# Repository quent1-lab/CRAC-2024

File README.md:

# Le LIDAR

Ce projet à été créer afin de répondre au besoin lié à la coupe de robotique de France 2024. Avec pour thème : Farming Mars

## Structure du projet

Le projet est organisé en plusieurs dossiers :

- `Lidar` : Contient le code python principal pour le fonctionnement du LIDAR. 
- `Lidarobot` : Contient le code C++ de la base roulante
- `PCB_CAN` : Contient le projet de la carte PCB CAN
- `Rapport S3` : Contient le rapport de projet
- `WIFI` : Contient des scripts simple pour tester la communication par socket et le principe du multitâche
- `CAN` : Contient un scripts simple pour tester la communication CAN
- `3D démonstrateur` : Contient les fichers STL et les GCODE correspondant à l'imprimante Ender-3 v2

## Installation

Vous pouvez cloner le projet via git en utilisant la commande suivante :

```bash
  git clone https://github.com/quent1-lab/CRAC-2024
```

Ensuite, naviguez dans le dossier du projet et installez les dépendances nécessaires avec pip :
```bash
  pip install -r requirements.txt
```
    
## Déploiement

Le fonctionnement de cette version du code nécessite un ordinateur connecté en série avec la base roulante, et le lidar connecté à la Raspberry Pi. 
Les deux appareils doivent être connecté au même réseau WIFI (Attention à bien modifier l'adresse IP du serveur sur le fichier `lidar_Rasp.py`).

Dans l'ordre, il faut lancer :
 - le programme python `LidarScan.py` sur l'ordinateur (car c'est le serveur)
```bash
  python Lidar/LidarScan.py
```
 - Le programme python `lidar_Rasp.py` sur la Raspberry Pi
```bash
  python Lidar/lidar_Rasp.py
```

## Authors

- [@quent1-lab](https://github.com/quent1-lab)

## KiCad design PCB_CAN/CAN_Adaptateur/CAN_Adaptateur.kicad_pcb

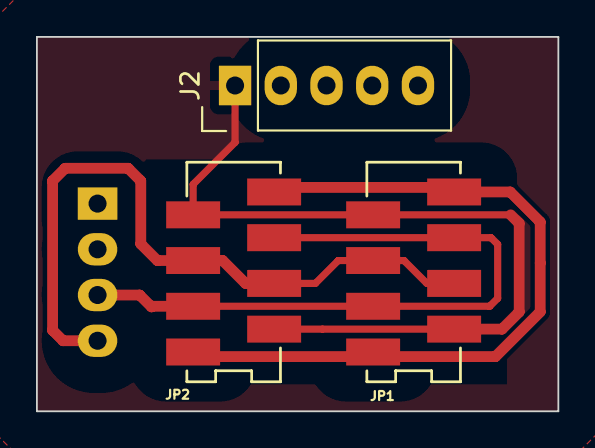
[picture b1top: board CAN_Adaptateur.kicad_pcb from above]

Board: 2 copper layers, 29.0 x 20.8 mm, 4 parts (1 on the bottom side), 3 nets.

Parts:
J1: Autocom4
J2: Autocom5
JP1: Can_1; MM 8 CMS F
JP2: Can_2; MM 8 CMS F

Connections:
/CAN_H: J1.4, JP1.4 (CAN_H), JP1.5 (CAN_H), JP2.4 (CAN_H), JP2.5 (CAN_H)
/CAN_L: J1.3, JP1.3 (CAN_L), JP1.6 (CAN_L), JP2.3 (CAN_L), JP2.6 (CAN_L)
GND: J2.1, JP1.2 (GND), JP1.7 (GND), JP2.2 (GND), JP2.7 (GND)

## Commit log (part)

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2024-05-05 chore: Activer l'asservissement lorsque le switch 3 est activé
2024-05-05 chore: Update CAN message ID for activating the asservissement
2024-05-05 chore: Update path to strategies folder in IHM_Robot.py
2024-05-05 chore: Update coordinates mapping in IHM and Lidar classes
2024-05-05 chore: Update LidarScanner class to remove unnecessary logging statement
2024-05-05 chore: Update LidarScanner class to adjust angle calculation
    ```
2024-05-05 chore: Update LidarScanner class angle calculation and coordinates mapping
2024-05-05 chore: Update coordinates mapping in LidarScanner class
2024-05-05 chore: Adjust angle calculation and remove unnecessary logging statement in LidarScanner class
2024-05-05 chore: Adjust angle calculation in LidarScanner class
2024-05-05 chore: Adjust angle calculation and update position update method in LidarScanner class
2024-05-05 chore: Refactor LidarScanner class position update method and angle calculation
2024-05-05 chore: Update Strategie class with timer functionality for stopping the strategy after a certain time
2024-05-05 chore: Update IHM_Robot class to use strategies from the strategies_cache directory
2024-05-05 chore: Update button position in IHM_Robot class
2024-05-05 chore: Update IHM_Robot class to include match page and points page
2024-05-06 chore: Update IHM_Robot class to include new buttons for recalibration
2024-05-06 chore: Update IHM_Robot class to reset PAGE value when zone is 0
2024-05-06 chore: Update IHM_Robot class to include lazy loading for images
2024-05-06 chore: Update button_recalage action in IHM_Robot class
2024-05-06 chore: Update button_recalage action and positions in IHM_Robot class
2024-05-06 chore: Update IHM_Robot class to include folder creation for recalages_cache
2024-05-06 chore: Update robot image scaling and position handling in IHM_Robot class
2024-05-06 chore: Update JSON files with new aknowledge values and modify CAN.py for set_odo command
2024-05-06 chore: Add logging statements for debugging CAN message handling
2024-05-06 chore: Update IHM_Robot.py for recalibration feature
2024-05-06 chore: Update CAN.py to send messageCan in ComCAN class
2024-05-06 chore: Update recalage_2.json for CAN recalibration feature
2024-05-06 chore: Update strategie.json and Lidar.py
2024-05-06 chore: Update Lidar.py to adjust angle range for scanning
2024-05-06 chore: Reset actionneur carte and start jack
2024-05-07 chore: Update IHM_Robot.py to display code version in the bottom right corner
2024-05-07 chore: Update IHM_Robot.py to adjust code version display position
2024-05-07 chore: Update IHM_Robot.py to remove unused imports and clean up code formatting
2024-05-07 chore: Update strategie.json and Lidar.py to handle empty data
2024-05-07 chore: Filter out low-quality lidar points in LidarScanner class
2024-05-07 chore: Update IHM_Robot.py to version 1.025
2024-05-07 chore: Update Lidar.py to filter out lidar points with quality below 530
2024-05-07 chore: Update Lidar.py to filter out lidar points with quality below 25
2024-05-07 chore: Update IHM_Robot.py to send the correct configuration message
2024-05-07 chore: Update Strategie.py to log received configuration and sent position
2024-05-07 chore: Bump IHM_Robot version to 1.027
2024-05-07 chore: Update Strategie.py to fix position calculation for yellow team
2024-05-07 chore: Update IHM_Robot.py and Lidar.py to improve LiDAR scanning process
2024-05-08 chore: Update Lidar.py detect_objects parameters for better object detection
2024-05-08 chore: Update Lidar.py to filter out points with significantly different distances from neighboring points
2024-05-08 chore: Update IHM_Robot.py version to 1.033 and run strategie 3 in Strategie.py
2024-05-08 Fix commented out code in Strategie.py
2024-05-08 chore: Update IHM_Robot.py version to 1.034
2024-05-08 Fix version number in IHM_Robot.py and update state assignment in Strategie.py
2024-05-08 chore: Add object drawing functionality in IHM_Robot.py
2024-05-08 Fix logging statement in Strategie.py to use single quotes for string interpolation
2024-05-08 chore: Update IHM_Robot.py version to 1.038 and add favorite buttons in IHM_Robot.py
2024-05-08 chore: Update IHM_Robot.py version to 1.039 and handle loading of strategy files
2024-05-08 chore: Update IHM_Robot.py to handle loading of strategy files and fix button action in Homologation
2024-05-08 feat: Update IHM_Robot.py version to 1.041 and handle recalibration in Homologation mode
2024-05-08 chore: Fix LidarScanner connection issue
2024-05-08 chore: Update LidarScanner class to filter points at a distance greater than 1000mm
2024-05-08 feat: Update IHM_Robot.py version to 1.042 and fix LidarScanner clustering thread start
2024-05-08 chore: Update LidarScanner class to improve connection stability and handle clustering thread start
2024-05-08 chore: Update LidarScanner class to log new scans and improve connection stability
2024-05-08 chore: Update LidarScanner class sleep times for better stability and performance
2024-05-08 chore: Update LidarScanner class sleep time for better stability and performance
2024-05-08 chore: Update LidarScanner class to log error in main and improve connection stability
2024-05-08 chore: Refactor LidarScanner class to optimize distance filtering
2024-05-08 chore: Update LidarScanner class to handle LiDAR status retrieval and error logging
2024-05-08 chore: Update LidarScanner class to adjust safety perimeter radius and handle LiDAR object detection
2024-05-08 chore: Add logging statements for object detection in LidarScanner class
2024-05-08 chore: Update Strategie class to pause robot when lidar state is "pause"
2024-05-08 chore: Update Strategie class to use dictionary for move message parameters
2024-05-08 chore: Réactiver la vérification de la position du robot dans la classe LidarScanner
2024-05-09 chore: Update BusCOM.py to log connection updates
2024-05-09 chore: Update LidarScanner class to handle object detection and robot movement
2024-05-09 chore: Update Lidar.py to filter points closer than 500mm to the robot
2024-05-09 chore: Update Strategie.py to fix end condition bug
2024-05-09 chore: Update windows.py to add Vitesse selection in IHM_Action_Aux class
2024-05-09 chore: Update IHM_Robot.py to increment version number to 1.046
2024-05-09 chore: Update code to filter points closer than 500mm to the robot
2024-05-09 chore: Update IHM_Robot.py to increment version number to 1.047 and update the number of points displayed
2024-05-09 chore: Update code to fix is_started flag and request energy at the end of the game
2024-05-09 chore: Charger la stratégie à partir d'un fichier spécifié
2024-05-09 chore: Update IHM_Robot.py to fix button action for index 4
2024-05-09 chore: Add logging for detected objects in LidarScanner
2024-05-09 chore: Update LidarScanner to filter Lidar points based on angle and distance
2024-05-09 chore: Update BusCOM.py to include new client name "STRAT"
2024-05-09 Charger la stratégie à partir d'un fichier spécifié
2024-05-09 chore: Update Lidar.py to filter Lidar points based on distance
    ```
2024-05-09 chore: Update IHM_Robot.py to increment version number and log object coordinates
2024-05-09 Log object coordinates when receiving objects data
2024-05-09 chore: Update IHM_Robot.py to handle objects data and log object coordinates
2024-05-09 Update Lidar.py to fix angle condition in LidarScanner
2024-05-09 chore: Update Lidar.py to fix condition for resuming movement when no objects are detected
2024-05-09 chore: Increment version number in IHM_Robot.py and update object coordinates logging
2024-05-09 chore: Réactiver l'asservissement dans la pause_en_mvt
2024-05-09 Mise à jour des fichiers de données et du code IHM
2024-05-09 chore: Update vitesse handling in strategie.py and strategie.json
2024-05-09 chore: Update vitesse handling in strategie.py
2024-05-10 Mise à jour de la vitesse et de l'image du terrain de jeu
2024-05-10 Mise à jour de la classe Strategie pour convertir les coordonnées en entiers
2024-05-10 Ajout de journaux de débogage pour les commandes de rotation et de déplacement en ligne droite
2024-05-10 chore: Update error handling in IHM_Robot.py and Lidar.py
2024-05-10 chore: Adjust detection conditions and handle lidar coordinate timeout
2024-05-10 chore: Update Strategie class to handle robot pause and resume actions
2024-05-10 chore: Update Strategie class to handle lidar stop flag
2024-05-10 chore: Update Strategie class to handle lidar stop flag and adjust detection conditions
2024-05-10 chore: Update Lidar.py to handle resume action and adjust detection conditions
2024-05-10 chore: Update Strategie class to adjust lidar coordinates and handle robot pause/resume actions
2024-05-10 chore: Update config_ordre_to_can.json to adjust ordre values for "Bras"
2024-05-10 chore: Update config_ordre_to_can.json and CAN.py to adjust ordre values and data format
2024-05-10 chore: Mettre à jour la classe Strategie pour ajuster les coordonnées du lidar et gérer les actions de pause/reprise du robot
2024-05-10 chore: Update Strategie class to adjust lidar coordinates and handle robot recalibration actions
2024-05-10 chore: Update config_ordre_to_can.json with new status value for "Aider"
2024-05-11 chore: Update sleep durations in Strategie class for better performance
2024-05-11 chore: Update Strategie class to adjust lidar coordinates for blue team
2024-05-11 chore: Update Strategie class to adjust lidar coordinates and handle robot recalibration actions for blue team
2024-05-11 chore: Update lidar coordinates and handle robot recalibration actions in Strategie class
2024-05-27 BusCOM V3
2024-06-02 Mettre à jour la classe IHM_Robot pour ajuster les coordonnées du lidar et gérer les actions de recalage du robot
2024-06-03 Fix bug dropdown closed
2024-06-04 chore: Mettre à jour les coordonnées de déplacement dans strategie.json et ajuster le dessin du chemin dans IHM.py
2024-06-05 Mettre à jour la classe IHM.py pour ouvrir une nouvelle fenêtre de configuration avec les valeurs de l'action suivante ou précédente
2024-06-08 chore: Mettre à jour la classe IHM.py pour commenter l'appel à self.programme_simulation()
2024-06-12 chore: Ajouter la fonctionnalité de chargement de stratégie dans IHM.py
2024-06-13 Mettre à jour la classe IHM.py pour commenter l'appel à self.programme_simulation()
2024-06-13 chore: Mettre à jour la classe IHM.py pour ajuster la conversion des coordonnées du scan Lidar
2024-06-13 chore: Supprimer les fichiers de stratégie obsolètes
2024-06-17 chore: Supprimer l'action de la stratégie et ajuster les numéros des actions suivantes
2024-06-19 Changement système de stratégie
2024-06-22 chore: Comment out unused code in IHM.py
2024-06-22 Ajout de la coord de l'action pour la reprise du lidar
2024-06-22 chore: Update logging error message in IHM_Robot.py
2024-06-22 chore: Update IHM_Robot.py to version 1.068 and add new buttons for PANNEAU and LEVER actions
2024-06-22 chore: Update IHM_Robot.py to version 1.069 and fix reprise of strategy
2024-06-22 chore: Update send_actions method in Strategie.py to accept optional akn parameter
2024-06-22 chore: Update Lidar.py to adjust distance threshold for filtering points
2024-06-22 chore: Update Strategie.py to fix reprise of strategy and logging messages
2024-06-22 chore: Update CAN.py to log the speed sent over the CAN bus
2024-06-22 chore: Ajouter des messages de journalisation pour la reprise de la stratégie après une pause en mouvement
2024-06-22 chore: Update IHM_Robot.py to display next points of the strategy
2024-06-23 chore: Update drawing of points on the screen in IHM_Robot.py
2024-06-23 chore: Update IHM_Robot.py to improve drawing of points on the screen
2024-06-23 chore: Clean up commented code in Strategie.py
2024-06-23 chore: Update IHM_Robot.py to version 1.075 and adjust drawing of points on the screen
2024-06-23 chore: Update IHM_Robot.py to version 1.076 and fix drawing of points on the screen
2024-06-23 chore: Update sleep duration in Strategie.py
2024-06-23 Modif affichage mouvement
2024-06-23 chore: Update IHM_Robot.py to version 1.079 and adjust drawing of points on the screen
2024-06-23 chore: Adjust drawing of points on the screen in IHM_Robot.py
